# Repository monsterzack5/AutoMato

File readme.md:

<!-- 
TODO: 
Talk more in depth about:
- Specially what CanRed does and can do
- Specially about the NodeRed wrapper
- Specially about how to actually make your own modules
- How we use the NodeRed API, and the NodeRed nodes we have implemented
- How to properly develop with this repo
- Talk more about subnetworks and where you'd use them.
 -->

Although near completely functional, AutoMato and generally everything in this repository are in an alpha state. Error handling and reliability are areas that are definitely lacking, and need to be improved before we can recommend actually using this inside of your car.

# AutoMato
A car specific framework for automation to breathe new life into an old car.

# About
We all have things we wish our car could do, especially if you have an older one. AutoMato seeks to give users the ability to program automations to make that happen. AutoMato is an extensible framework that allows users to create modules that control features of the car based on events or user input. 

AutoMato implements 3 things to help abstract away all the complexities of car automation:
- ## AutoMato Embedded Library
  - Provides an easy yet powerful way for user created modules to talk to the rest of the AutoMato framework, along with options to customize and extend it.

- ## CanRed
  - The centralized control program for all the modules, handles communication between the modules and Node Red along with fundamental infrastructure that is necessary for the system to function.

- ## NodeRed Integration
  - An intuitive interface that allows you to easily build event based automation flows using a flowchart style interface.

## Modules
Modules are pieces of hardware that contain a microcontroller and specific circuitry to control features of the car such as the windows, climate controls, or windshield wipers. Modules can be connected together via CANBUS or serial by default, but other interfaces can be added in through our library. Modules can be powered all the time (S0) or can be powered only when the car is in ACC (S1). It is planned to have a module to make the car go into ACC to access any S1 modules that are in an offline flow.

users are encouraged to control as much as they can with a single module due to power draw. Simply put, the fewer modules the car has the less quiescent current will be drawn when the car is off.

## Automation

Automation flows can be created very easily using NodeRed and the AutoMato plugin for it. The modules that are connected to the system will be added dynamically to the interface with the help of CanRed when you add them to the network.

There are two types of flows that can be created:
- ### Online Event Flows
Online event flows require the SBC (ex: Raspberry Pi) to be powered up in order for them to work. These are generally meant to be used only when the car is running because it has a high power draw. With this configuration, NodeRed is actively handling module events and issuing commands. This allows you to use the powerful existing library of NodeRed nodes with your flows.  
For example: using a PID control node for the cabin temperature of your car.
- ### Offline Event Flows
Offline event flows can be run when the car is on or off, allowing you to have flows that can be run 24/7. These are compiled from NodeRed into "Event Blocks" and spread throughout the modules used in the flow.  
For example: using a rain sensor to roll up the windows in your car.

# Documentation
Information about specific systems and general development info can be found in `/Documentation`.
The docs are only loosely organized and are by no-means extensive. In the future, as more systems get ironed out, documentation will improve drastically.

# How to Use
In the "finished" system, CanRed and NodeRed are both ideally ran on an SBC (ex: Raspberry Pi) inside of your car with the ability to turn itself off to conserve power. As mentioned above, modules can either be connected to a fulltime 12v source, or the cars ACC line. CanRed can be linked to the modules via a CANBUS network or the modules can be daisy chained to each other via Serial. You can even mix and match depending on what is best suited for your application.

Modules are intended to be user programmed, where the user can create specific functions to do specific tasks, and then register these with the AutoMato library so that they can be called from anywhere. A rough example of that:
```cpp
AutomatoReturnData LockAllCarDoors(const void*)
{
    bool did_doors_lock = lock_all_the_doors();

    if (did_doors_lock) {
        return automato_return(true);
    } else {
        return automato_return(false);
    }
}

int main() {
    Automato automato(configuration_string);

    // The "1" here corresponds to the ID of the function,
    // ideally you'll be able to leave this out in the future.
    automato.register_callback(1, LockAllCarDoors);

    while (true) {
        automato.loop();
        // Other user specific code here
    }
}
```

# Working Features
- [x] Module to central controller communication (Star Networking)
- [x] Supports Zephyr and Arduino frameworks
- [x] JSON based unix socket API (Working, but very limited)
- [x] Module linking via Serial or CANBUS
- [x] "Online" Automation, using NodeRed
- [x] "Offline" Automation, without needing NodeRed
- [x] Independent sub-networks
- [x] Easily extensible API for modifying several parts of the system.

# Planned / In Development
- [ ] Module to module communication (This works for the event system, but not for user functions)
- [ ] Module health checks (Currently half-baked)
- [ ] An easy to use error system, where module runtime errors can be sent to CanRed
- [ ] Many more JSON IPC features
- [ ] Integrating with other Automation frameworks, such as HomeAssistant
- [ ] Integrating a SIM7000A module for LTE/CAT-M1 network contectivity
- [ ] Support for STM32Cube and Expressif frameworks

# Going into a bit more depth
- ## Online and Offline Automation
  - ### Online Automation Flows
    - flows that are created inside of NodeRed using online event nodes. These flows can use any NodeRed nodes including third party ones. We utilize CanRed to read the message from the module, interpret which node it is from, and tell NodeRed that an event happened. For commands, NodeRed sends the command to the correct module based on the information provided in the node to CanRed.

  - ### Offline Automation Flows
    - flows that are also created inside of NodeRed except users must use offline event nodes. These flows are limited to other offline event nodes as they need to be parsed and compiled into "Event Blocks" that are saved to the modules. When an "Event Block" is triggered, the initilization module runs a command and/or sends a command to another module with an event ID. That module will then run its own "Event Block". This will continue until the flow has completed. NodeRed simply acts as an interface to construct these offline flows, it is not actively involved in the flows as the modules communicate in a mesh style.

- ## JSON UNIX Socket API
CanRed creates and listens to any socket connections to `/tmp/CanRed/red.sock`. This API can be used as an IPC system for any other programs running on the Raspberry Pi. Internally it's how NodeRed talks to CanRed, and vise versa.

- ## Independent Sub-networks
Modules can be connected to each other in all sorts of ways, this allows flexibility and the ability to overcome device number limits on busses if neccessary.

For example, this is a perfectly valid setup:
```
                                                ------------            ----------------
                                             >  | Module 2 | <-CANBUS-> | Non-Automato |
                                             |  ------------            |    Module    |
----------            ------------           |  ------------            ----------------
| CanRed | <-Serial-> | Module 1 | <- CANBUS +> | Module 3 | 
----------            ------------           |  ------------
                            ^                |  ------------
                            |                >  | Module 4 |
                            |                   ------------
                            | Serial
                            |   ------------    
                            - > | Module 5 |
                                ------------
```
Using the `translate_between_layers` API, you can have multiple networks and sub-networks happily interact with each other.

- ## Easily extensible API
Currently this system uses runtime-polymorphism since it was the easiest to implement, but avoiding the overhead of vtables is planned in the future. __The API is subject to drastically change in the future__.  

Although the AutoMato library tries to implement specialized wrapper code for interacting with EEPROM and connecting to a network (Like CANBUS/Serial), sometimes you want to be able to use something else, LINBUS or Z-Wave. We allow users to be able to implement this themselves by passing the implementation to either the AutoMato constructor (in the case of a custom EEPROM or NVS implementation) or by using the `.add_interface` API for custom bus interfaces.

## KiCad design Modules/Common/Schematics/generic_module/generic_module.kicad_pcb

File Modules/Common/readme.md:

# This folder contains libraries that are common between Modules.

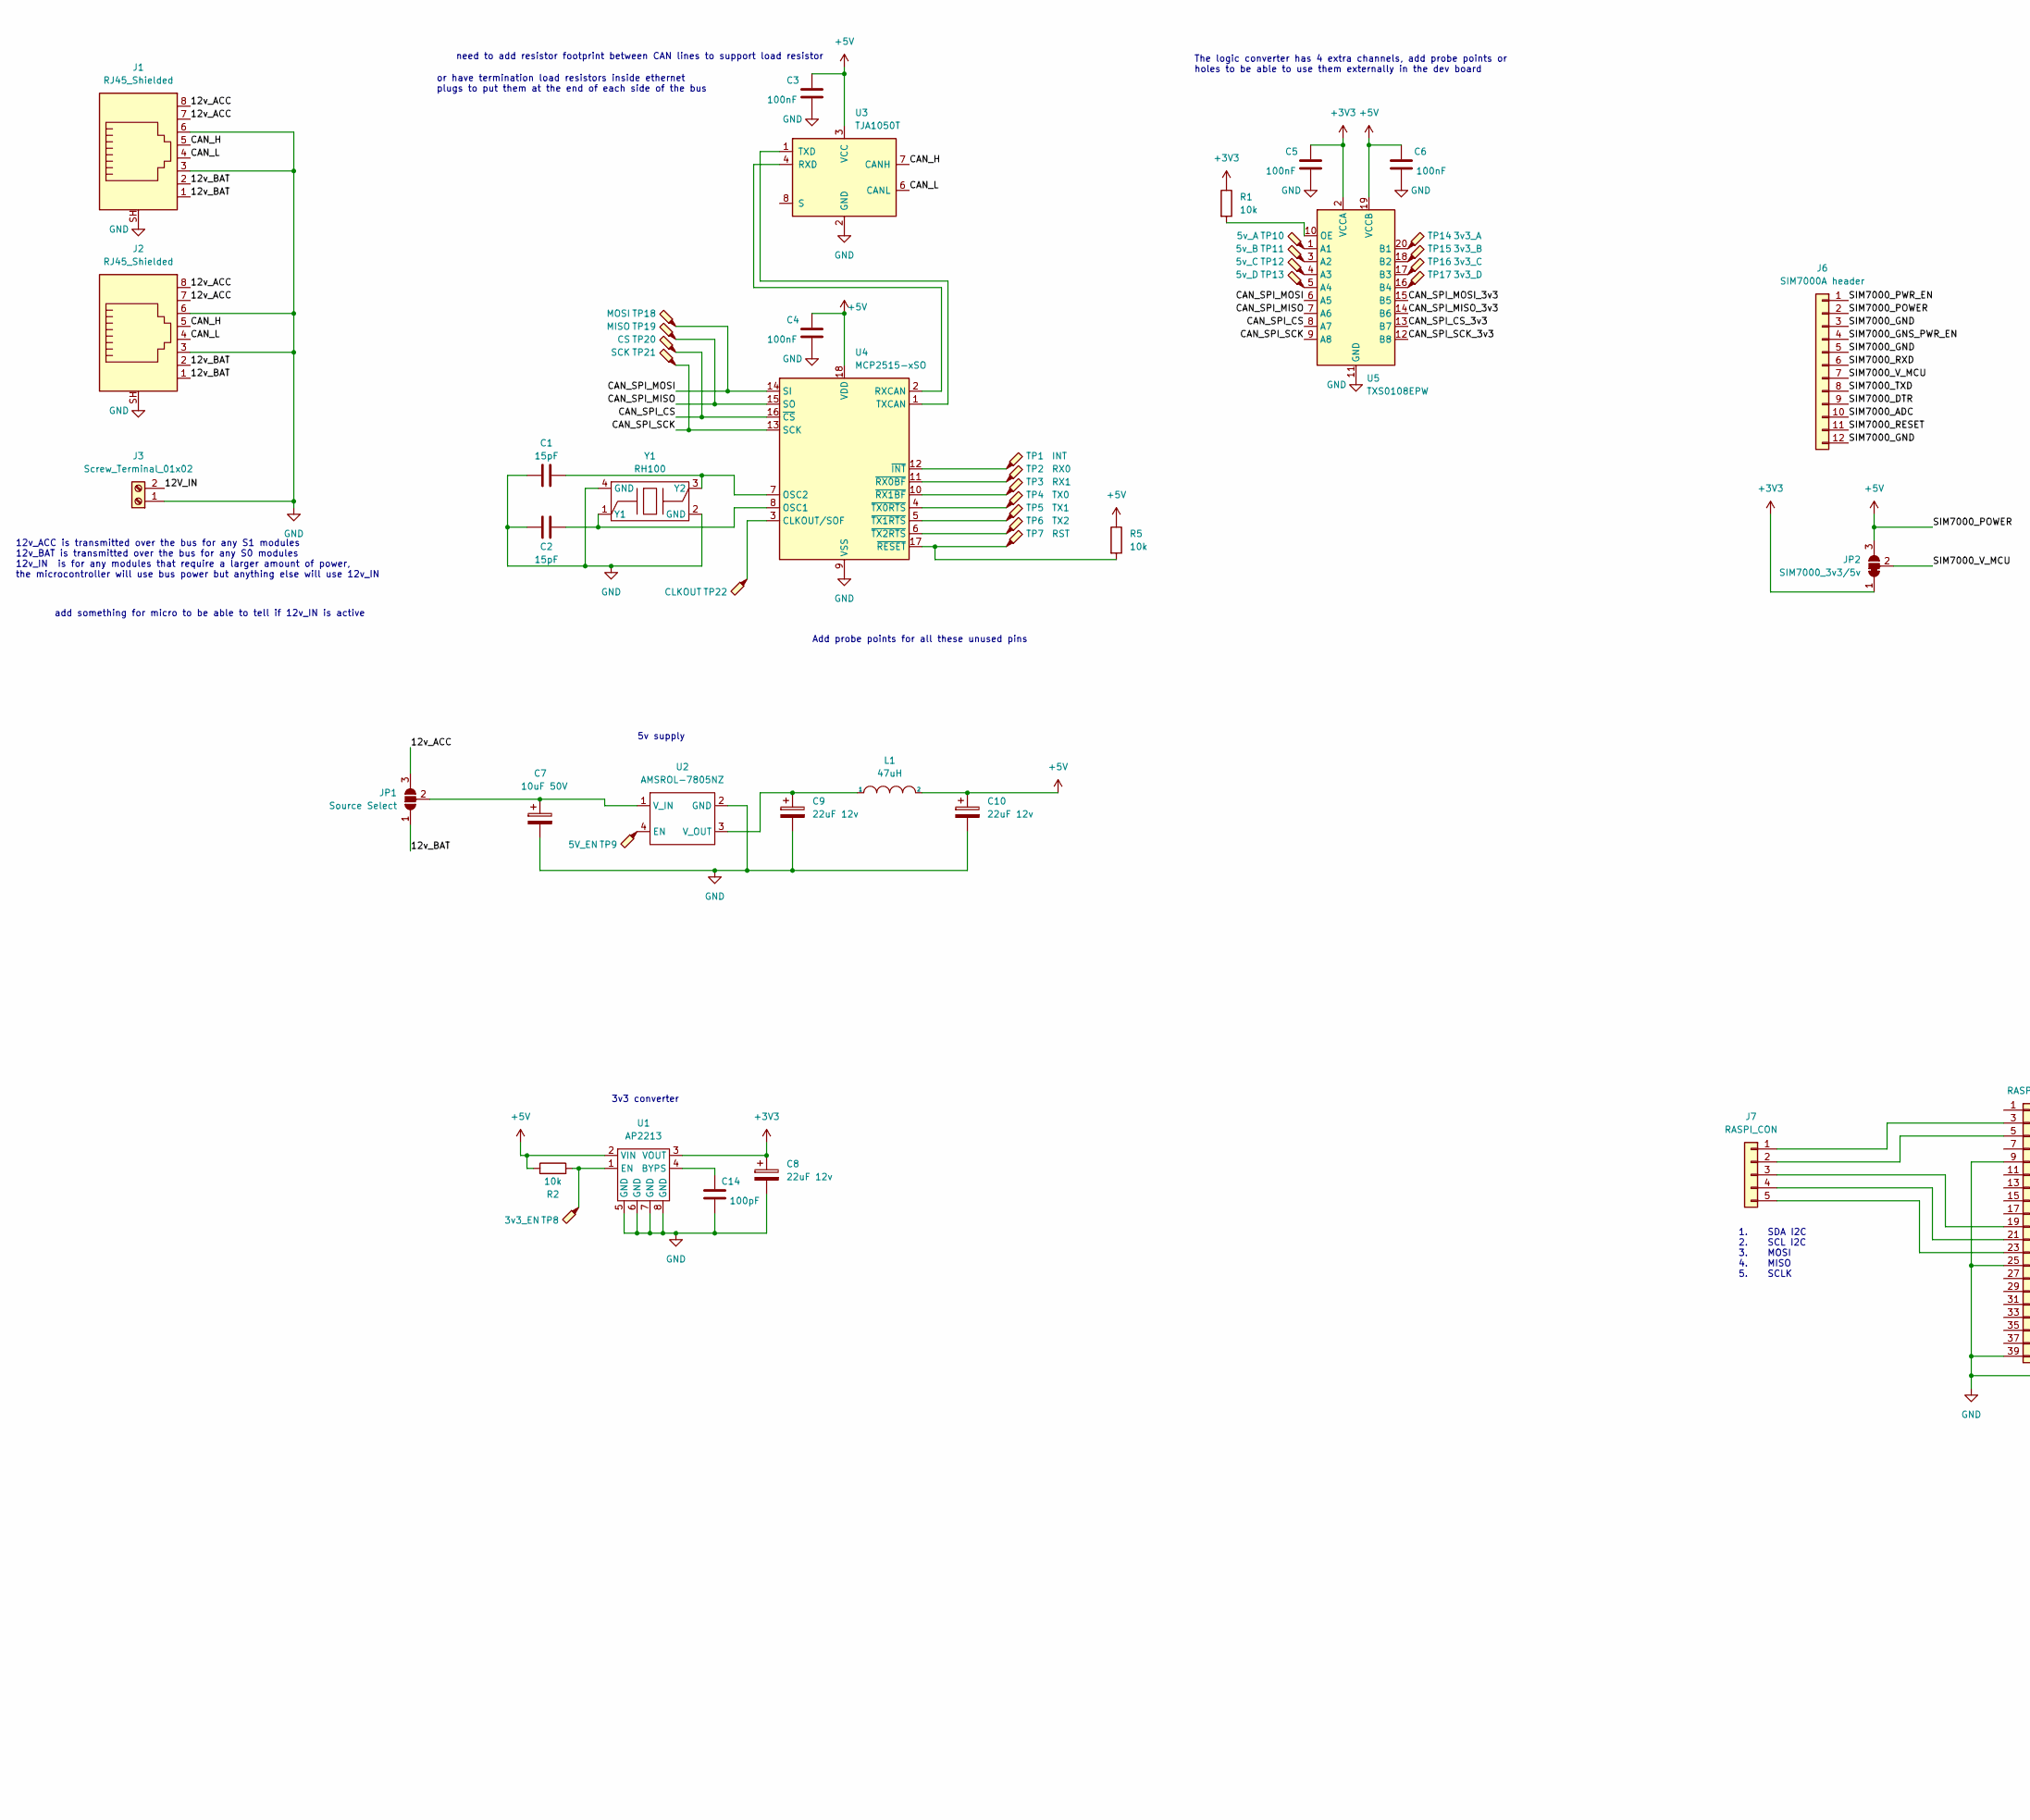
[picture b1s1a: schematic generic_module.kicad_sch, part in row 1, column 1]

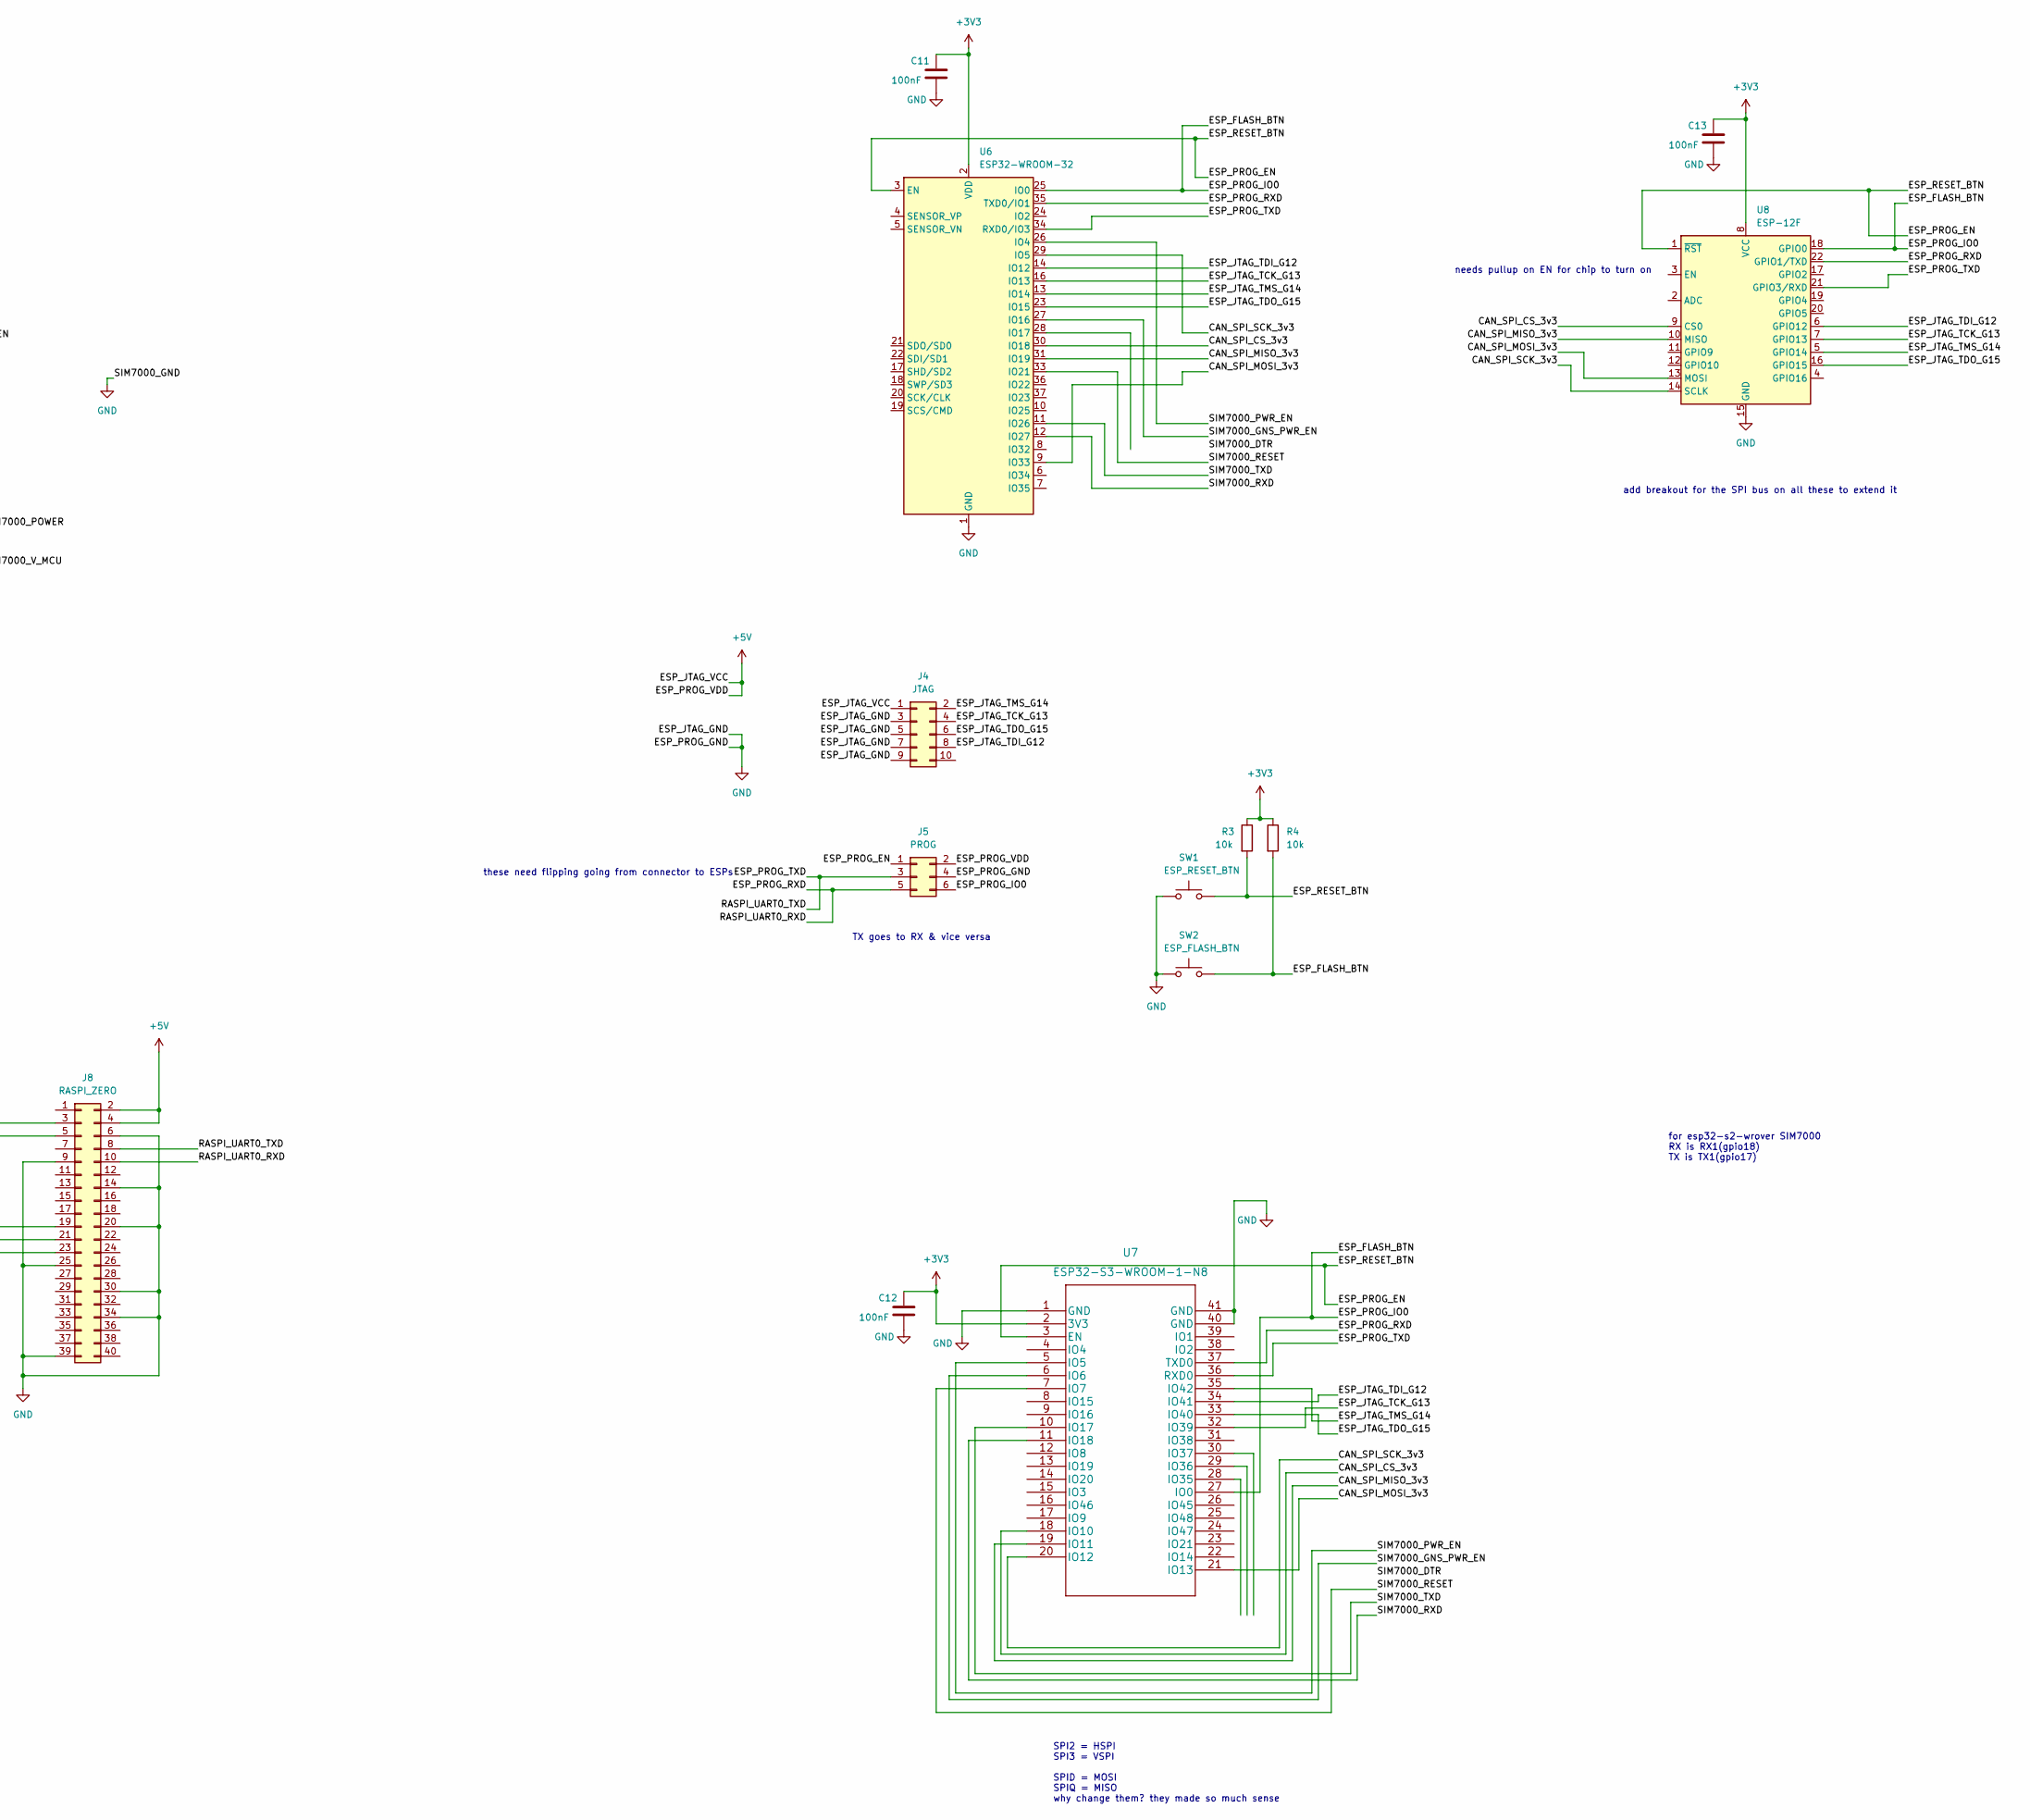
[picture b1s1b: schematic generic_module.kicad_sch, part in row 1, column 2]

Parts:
C1, C2: 15pF; C_1206_3216Metric_Pad1.33x1.80mm_HandSolder
C3, C4, C5, C6, C11, C12, C13: 100nF; C_1206_3216Metric_Pad1.33x1.80mm_HandSolder
C7: 10uF 50V; CP_Radial_D6.3mm_P2.50mm
C8, C9, C10: 22uF 12v; CP_Radial_D6.3mm_P2.50mm
C14: 100pF; C_1206_3216Metric_Pad1.33x1.80mm_HandSolder
J1, J2: RJ45_Shielded; RJ45_Ninigi_GE
J3: Screw_Terminal_01x02; TerminalBlock_bornier-2_P5.08mm
J4: JTAG; PinHeader_2x05_P1.27mm_Vertical
J5: PROG; PinHeader_2x03_P1.27mm_Vertical
J6: SIM7000A header; SIM7000_MODULE
J7: RASPI_CON; PinSocket_1x05_P2.54mm_Vertical
J8: RASPI_ZERO; RASPI_ZERO(W)
JP1: Source Select; SolderJumper-3_P1.3mm_Open_Pad1.0x1.5mm
JP2: SIM7000_3v3/5v; SolderJumper-3_P1.3mm_Bridged2Bar12_Pad1.0x1.5mm
L1: 47uH; SDEI054T
R1, R2, R3, R4, R5: 10k; R_1206_3216Metric_Pad1.30x1.75mm_HandSolder
SW1: ESP_RESET_BTN; SW_PUSH_6mm
SW2: ESP_FLASH_BTN; SW_PUSH_6mm
TP1: INT; TestPoint_Pad_D2.0mm
TP2: RX0; TestPoint_Pad_D2.0mm
TP3: RX1; TestPoint_Pad_D2.0mm
TP4: TX0; TestPoint_Pad_D2.0mm
TP5: TX1; TestPoint_Pad_D2.0mm
TP6: TX2; TestPoint_Pad_D2.0mm
TP7: RST; TestPoint_Pad_D2.0mm
TP8: 3v3_EN; TestPoint_Pad_D2.0mm
TP9: 5V_EN; TestPoint_Pad_D2.0mm
TP10: 5v_A; TestPoint_Pad_D2.0mm
TP11: 5v_B; TestPoint_Pad_D2.0mm
TP12: 5v_C; TestPoint_Pad_D2.0mm
TP13: 5v_D; TestPoint_Pad_D2.0mm
TP14: 3v3_A; TestPoint_Pad_D2.0mm
TP15: 3v3_B; TestPoint_Pad_D2.0mm
TP16: 3v3_C; TestPoint_Pad_D2.0mm
TP17: 3v3_D; TestPoint_Pad_D2.0mm
TP18: MOSI; TestPoint_Pad_D2.0mm
TP19: MISO; TestPoint_Pad_D2.0mm
TP20: CS; TestPoint_Pad_D2.0mm
TP21: SCK; TestPoint_Pad_D2.0mm
TP22: CLKOUT; TestPoint_Pad_D2.0mm
U1: AP2213; SOIC-8_3.9x4.9mm_P1.27mm
U2: AMSROL-7805NZ; amsrol_78XXnz
U3: TJA1050T; SOIC-8_3.9x4.9mm_P1.27mm
U4: MCP2515-xSO; SOIC-18W_7.5x11.6mm_P1.27mm
U5: TXS0108EPW; TSSOP-20_4.4x6.5mm_P0.65mm
U6: ESP32-WROOM-32
U7: ESP32-S3-WROOM-1-N8
U8: ESP-12F; ESP-12E
Y1: RH100

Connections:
+3V3: C5.1, C8.1, C11.1, C12.1, C13.1, JP2.1 (A), R1.1, R3.1, R4.1, U1.3 (VOUT), U5.2 (VCCA), U6.2 (VDD), U7.2 (3V3), U8.8 (VCC); also elsewhere on the board
/12V_IN: J3.2
/12v_ACC: J1.7, J1.8, J2.7, J2.8, JP1.3 (B)
/12v_BAT: J1.1, J1.2, J2.1, J2.2, JP1.1 (A)
/CAN_H: J1.5, J2.5, U3.7 (CANH)
/CAN_L: J1.4, J2.4, U3.6 (CANL)
/CAN_SPI_CS: TP20.1, U4.16 (~CS), U5.8 (A7)
/CAN_SPI_CS_3v3: U5.13 (B7), U6.30 (IO18), U7.18 (IO10), U8.9 (CS0)
/CAN_SPI_MISO: TP19.1, U4.15 (SO), U5.7 (A6)
/CAN_SPI_MISO_3v3: U5.14 (B6), U6.31 (IO19), U7.19 (IO11), U8.10 (MISO)
/CAN_SPI_MOSI: TP18.1, U4.14 (SI), U5.6 (A5)
/CAN_SPI_MOSI_3v3: U5.15 (B5), U6.9 (IO33), U7.21 (IO13), U8.13 (MOSI)
/CAN_SPI_SCK: TP21.1, U4.13 (SCK), U5.9 (A8)
/CAN_SPI_SCK_3v3: U5.12 (B8), U6.29 (IO5), U7.20 (IO12), U8.14 (SCLK)
/ESP_FLASH_BTN: J5.6, R4.2, SW2.2, U6.25 (IO0), U7.27 (IO0), U8.18 (GPIO0); also elsewhere on the board
/ESP_JTAG_TCK_G13: J4.4, U6.16 (IO13), U7.32 (IO39), U8.7 (GPIO13)
/ESP_JTAG_TDI_G12: J4.8, U6.14 (IO12), U7.34 (IO41), U8.6 (GPIO12)
/ESP_JTAG_TDO_G15: J4.6, U6.23 (IO15), U7.33 (IO40), U8.16 (GPIO15)
/ESP_JTAG_TMS_G14: J4.2, U6.13 (IO14), U7.35 (IO42), U8.5 (GPIO14)
/ESP_PROG_EN: J5.1, R3.2, SW1.2, U6.3 (EN), U7.3 (EN), U8.1 (~RST); also elsewhere on the board
/ESP_PROG_RXD: J5.5, J8.10, U6.35 (TXD0/IO1), U7.37 (TXD0), U8.22 (GPIO1/TXD)
/ESP_PROG_TXD: J5.3, J8.8, U6.34 (RXD0/IO3), U7.36 (RXD0), U8.21 (GPIO3/RXD)
/SIM7000_ADC: J6.10
/SIM7000_DTR: J6.9
/SIM7000_GNS_PWR_EN: J6.4, U6.27 (IO16), U7.6 (IO6)
/SIM7000_PWR_EN: J6.1, U6.26 (IO4), U7.5 (IO5)
/SIM7000_RESET: J6.11, U6.33 (IO21), U7.7 (IO7)
/SIM7000_RXD: J6.6, U6.12 (IO27), U7.11 (IO18)
/SIM7000_TXD: J6.8, U6.11 (IO26), U7.10 (IO17)
/SIM7000_V_MCU: J6.7, JP2.2 (C); also elsewhere on the board
GND: C1.1, C2.2, C3.2, C4.2, C5.2, C6.2, C7.2, C8.2, C9.2, C10.2, C11.2, C12.2, C13.2, C14.2, J1.3, J1.6, J1.SH, J2.3, J2.6, J2.SH, J3.1, J4.3, J4.5, J4.7, J4.9, J5.4, J6.3, J6.5, J6.12, J8.6, J8.9, J8.14, J8.20, J8.25, J8.30, J8.34, J8.39, SW1.1, SW2.1, U1.5 (GND), U1.6 (GND), U1.7 (GND), U1.8 (GND), U2.2 (GND), U3.2 (GND), U4.9 (VSS), U5.11 (GND), U6.1 (GND), U6.15 (GND), U6.38 (GND), U6.39 (GND), U7.1 (GND), U7.40 (GND), U7.41 (GND), U8.15 (GND), Y1.2 (GND), Y1.4 (GND); also elsewhere on the board
unnamed: C1.2, U4.7 (OSC2), Y1.3 (Y2)
unnamed: C2.1, U4.8 (OSC1), Y1.1 (Y1)
unnamed: C7.1, JP1.2 (C), U2.1 (V_IN)
unnamed: C9.1, L1.1, U2.3 (V_OUT)
unnamed: J7.1, J8.3
unnamed: J7.2, J8.5
unnamed: J7.3, J8.19
unnamed: J7.4, J8.21
unnamed: J7.5, J8.23
unnamed: R1.2, U5.10 (OE)
unnamed: R5.2, TP7.1, U4.17 (~RESET)
unnamed: TP1.1, U4.12 (~INT)
unnamed: TP2.1, U4.11 (~RX0BF)
unnamed: TP3.1, U4.10 (~RX1BF)
unnamed: TP4.1, U4.4 (~TX0RTS)
unnamed: TP5.1, U4.5 (~TX1RTS)
unnamed: TP6.1, U4.6 (~TX2RTS)
unnamed: TP9.1, U2.4 (EN)
unnamed: TP10.1, U5.1 (A1)
unnamed: TP11.1, U5.3 (A2)
unnamed: TP12.1, U5.4 (A3)
unnamed: TP13.1, U5.5 (A4)
unnamed: TP14.1, U5.20 (B1)
unnamed: TP15.1, U5.18 (B2)
unnamed: TP16.1, U5.17 (B3)
unnamed: TP17.1, U5.16 (B4)
unnamed: TP22.1, U4.3 (CLKOUT/SOF)
unnamed: R2.2, TP8.1, U1.1 (EN)
unnamed: C14.1, U1.4 (BYPS)
unnamed: U3.1 (TXD), U4.1 (TXCAN)
unnamed: U3.4 (RXD), U4.2 (RXCAN)

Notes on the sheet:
or have termination load resistors inside ethernet plugs to put them at the end of each side of the bus
12v_ACC is transmitted over the bus for any S1 modules 12v_BAT is transmitted over the bus for any S0 modules 12v_IN is for any modules that require a larger amount of power, the microcontroller will use bus power but anything else will use 12v_IN
The logic converter has 4 extra channels, add probe points or holes to be able to use them externally in the dev board
add something for micro to be able to tell if 12v_IN is active
1. SDA I2C 2. SCL I2C 3. MOSI 4. MISO 5. SCLK
SPI2 = HSPI SPI3 = VSPI SPID = MOSI SPIQ = MISO why change them? they made so much sense
these need flipping going from connector to ESPs
add breakout for the SPI bus on all these to extend it
for esp32-s2-wrover SIM7000 RX is RX1(gpio18) TX is TX1(gpio17)
Add probe points for all these unused pins
3v3 converter
need to add resistor footprint between CAN lines to support load resistor
needs pullup on EN for chip to turn on
5v supply
TX goes to RX & vice versa

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
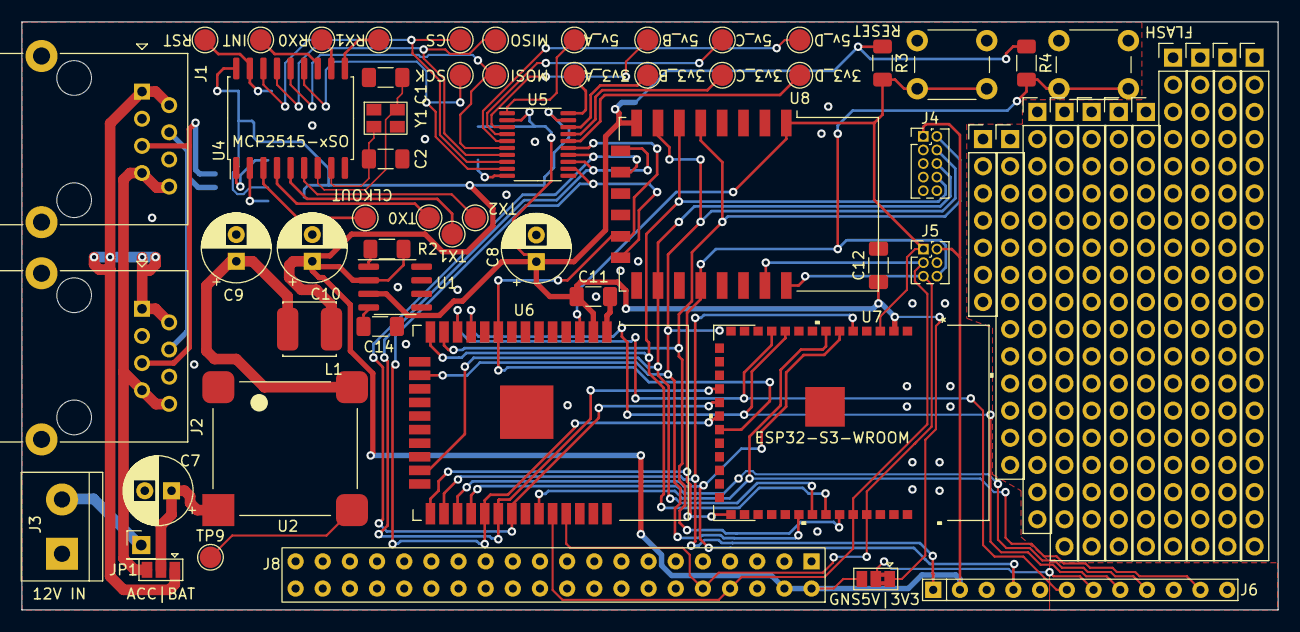
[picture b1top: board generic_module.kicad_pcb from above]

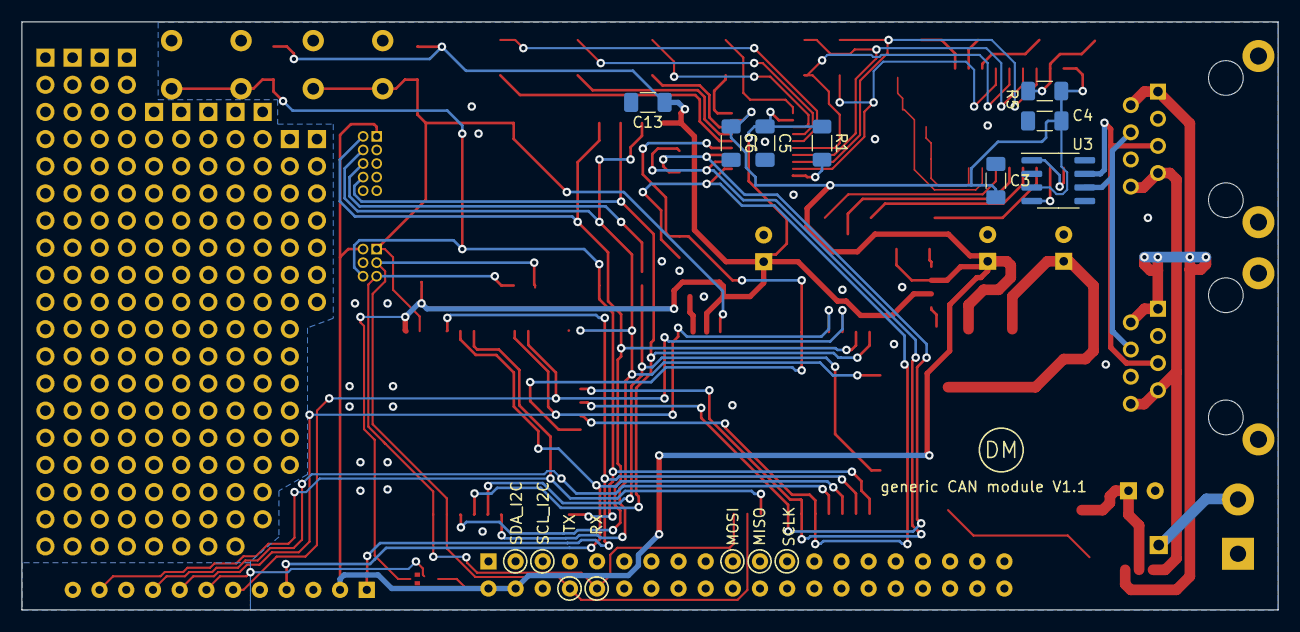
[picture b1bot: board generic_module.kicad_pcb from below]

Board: 2 copper layers, 117.5 x 55.0 mm, 72 parts (8 on the bottom side), 55 nets.

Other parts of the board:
 : PinHeader_1x19_P2.54mm_Vertical
 #2: PinHeader_1x07_P2.54mm_Vertical
 #3: PinHeader_1x13_P2.54mm_Vertical
 #4,  #7,  #8: PinHeader_1x19_P2.54mm_Vertical
 #5,  #6,  #9,  #10: PinHeader_1x17_P2.54mm_Vertical
 #11: PinHeader_1x16_P2.54mm_Vertical
FLASH: ESP_FLASH_BTN; SW_PUSH_6mm
GNS5V|3V3: SIM7000_3v3/5v; SolderJumper-3_P1.3mm_Bridged2Bar12_Pad1.0x1.5mm
RESET: ESP_RESET_BTN; SW_PUSH_6mm

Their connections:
+3V3: GNS5V|3V3.1 (A); also elsewhere on the board
/ESP_FLASH_BTN: FLASH.2; also elsewhere on the board
/ESP_PROG_EN: RESET.2; also elsewhere on the board
/SIM7000_V_MCU: GNS5V|3V3.2 (C); also elsewhere on the board
GND: FLASH.1, RESET.1; also elsewhere on the board

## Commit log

2022-07-12 CanRed: Initial Commit :^)
2022-07-12 Common: Initial Commit :^)
2022-07-12 Documentation: Initial Commit :^)
2022-07-12 Modules: Initial Commit :^)
2022-07-12 NodeRed: Initial Commit :^)
2022-07-12 Scripts: Initial Commit :^)
2022-07-12 Chore: update root .gitignore to properly ignore root scratchpad folder
2022-07-13 Documentation: Add a nice readme into the project root
2022-07-13 KeyFob: Add a nice readme
2022-07-13 Keyfob: fix readme.md image links
2022-07-13 Keyfob: Convert both keyfob images into just one image
2022-07-14 Documentation: Add Modules/readme.md, and Schematic files.
2022-07-14 Chore: remove .clang-format and .vscode folder from Modules/Common
2022-07-14 Util: Make zephyr version of print_u8_array() inline
2022-07-14 Keyfob/Remote: Refactoring
    - Implement MessageParams, for easier handling of IV/RollingCode
    - Convert iv_and_rolling_code* functions to use MessageParams
    - Remove some unneeded comments
    - Remove iv and rolling_code global variables
    - Enable using powerstates again
2022-07-14 Keyfob/Remote: Enable Debounce
2022-07-15 Keyfob/Remote+Keyfob/Crypto: Move Crypto Functions to a Library
    - Create ZephyrAesGCM.cpp in Common/Crypto
    - Move encrypt function from remote/main.cpp to ZephyrAesGCM.cpp
    - Move MessageParameters to KeyfobConfig.h
2022-07-15 Keyfob/Common: Convert printk calls to LOG_ERR
2022-07-15 Keyfob/Module: Implement Crypto+MessageParams
    Bring LoraModule up to speed with LoraRemote
    - Implement MessageParams
    - Remove Local crypto function
    - Use ZephyrAesGCM crypto functions
2022-07-15 Documentation: Update and rename overview.md
2022-07-15 Documentation: Update Formating for Github
2022-07-15 Modules: Add TempSensor as an example project
2022-07-16 Improved ReadMe (#1)
    * Update readme.md
2022-07-17 Modules/keyfob: Switch to using a custom board configuration
    This custom board config is from the Zephyr repo at commit hash:
    106f82013bfb153e82c5d2f537cf568c5b2ad13f
    This is the newest commit we can use, since after this they
    implemented CONFIG_PINCTRL into all stm32 boards, which
    is not currently supported on the version of Zephyr PlatformIO
    is limited to.
2022-07-17 Modules/Keyfob: Implement all buttons using an Overlay
2022-07-17 Modules/Keyfob: Move PM Functions to their own functions
2022-07-17 Modules/Keyfob: Share init_flash() and init_lora()
2022-07-17 Modules/Keyfob: Convert to using an Overlay for GPIO
2022-08-20 CanRed/Chore: Make sure -wal files are excluded from git
2022-08-20 Chore: Copy .clang-format to root folder
    Some IDE's are unhappy if they cannot find a clang format file
    by traversing backwards through the filesystem. Which happens
    when you're editing a library file with no .clang-format inside
    of the libraries src directory.
2022-08-20 Modules: simplify comparing AnyType's
2022-08-20 Modules: Maintain consistency with other AnyType functions
2022-08-21 Modules: Move {type_used,event_type} to Event.h
2022-08-21 Modules: Replace ifdef CANRED with PLATFORM_DESKTOP
2022-09-06 Events: Fix #include formatting
2022-09-06 Util: Don't try and center any binary output
2022-09-06 Events: Convert if/else chain to lookup table
2022-09-06 Modules/Automato: Fixed not checking all main events
2022-09-06 Modules/Automato: Move interfaces to their own folder
2022-09-06 Modules/Automato: Move frame vetting and ACK handling to InterfaceHandler
2022-09-06 Modules/Automato: Create InterfaceHandler class
    Create InterfaceHandler, which handles:
    - ACK's" sending them, checking them, removing them
    - Node UID: storing/saving the current nodes UID
    - Keeping track of interfaces
    - sending/getting frames from interfaces
    This removes a lot of complexity, and about 400 lines of code
2022-09-06 Modules/InterfaceHandler: Make ACK Functions Private
    InterfaceHandler should be the only class that has to deal
    with ACKs from this point foward. This reduces complexity inside
    of Automato.h and generally makes Automato functions neater.
2022-09-07 Modules/Automato: Create LongFrameHandler.h
    This is a helper class that interfaces with LongFrames.
    Previously, Automato.h handled LongFrames which required
    several functions, a 2d array and a 1d array. Moving the complexity
    from Automato.h to LongFrameHandler helps to further simplify
    Automato.h
2022-09-07 Modules/Automato: Create CommandHandler.h
    This header-only class deals with registering command
    functions and being able to call those functions using
    their command_id.
    Previously, these functions were contained inside of Automato.h,
    which also required having a c-style array to store the function
    pointers and their command_id's. The new CommandHandler class

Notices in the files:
parts and their libraries:
Copyright 2021 Accelerated Designs. All rights reserved.
